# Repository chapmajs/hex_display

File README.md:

PIC Based Mutiplexed 7-segment LED Display
==========================================

A project to drive multiplexed 7-segment LED displays as hex displays using a Microchip PIC18F6310 with a minimum of external components. This is a work in progress!

This project is released as [Open Source Hardware (OSHW)](http://freedomdefined.org/OSHW). All hardware contained within this repository are covered by a [Creative Commons Attribution-ShareAlike 3.0 license (CC BY-SA 3.0)](http://creativecommons.org/licenses/by-sa/3.0/). Firmware and software are licensed under GPLv3 -- see LICENSE and GPL-3.0 for more information.

### Current Status

Rev 0 PC board has been tested, sample firmware in this repository displays 'deadbeef'. Minor tweaks to the PC board layout are required for 0.1" perfboard compatibility. 24-bit port input has not yet been tested.

### Why?

"Intelligent" single-nybble hexadecimal displays like the TIL311 are available, as well as 7-segment hex decoders; however, these devices are no longer in production and they're expensive, when you can find them. The 7-segment hex decoders that are currently available handle single displays only and don't work with multi-character multiplexed displays.

### How?

This display project implements a multi-character bitmapped display using an interrupt-driven subroutine to handle multiplexing. A display buffer is used to simplify loading data for display. Character selection was delegated to a subroutine that enables the appropriate cathode driver pin based on an offset. This allows the size of the display to be changed with minimal firmware modification.

A PIC microcontroller with plenty of I/O was chosen to allow input of 24 bits of binary data in parallel (16 bit address + 8 bit data, a common arrangement with old 8-bit processors like the Intel 8080/8085, Zilog Z80, or MOS 6502). Using this device as a debugging tool was the primary goal; however, it was designed in such a way that the PIC's onboard devices can also act as data sources for the display. It's possible to display data from I2C, SPI, RS-232, parallel port, or ADC sources. Additionally, one could drive dot matrix displays with the same firmware.

An in-memory lookup table provides translation from single hex nybbles to appropriate bitmap patterns for 7-segment displays. A routine utilizing this table can be called from firmware to produce hex digits if bitmap characters are not desired.

### Who?

[The Glitch Works](http://www.glitchwrks.com/)

There's a thread on the [BinRev Forums](http://www.binrev.com/forums/index.php/topic/46160-hex-display-project/) for discussion

### Files

* display.asm: PIC18F6310 firmware for driving mutiplexed common cathode 7-segment displays
* pinouts.md: PC board connector pinouts
* schematic.sch: Eagle CAD schematic
* schematic.brd: Eagle CAD board layout
* eagle_libs: Directory containing nonstandard Eagle CAD parts

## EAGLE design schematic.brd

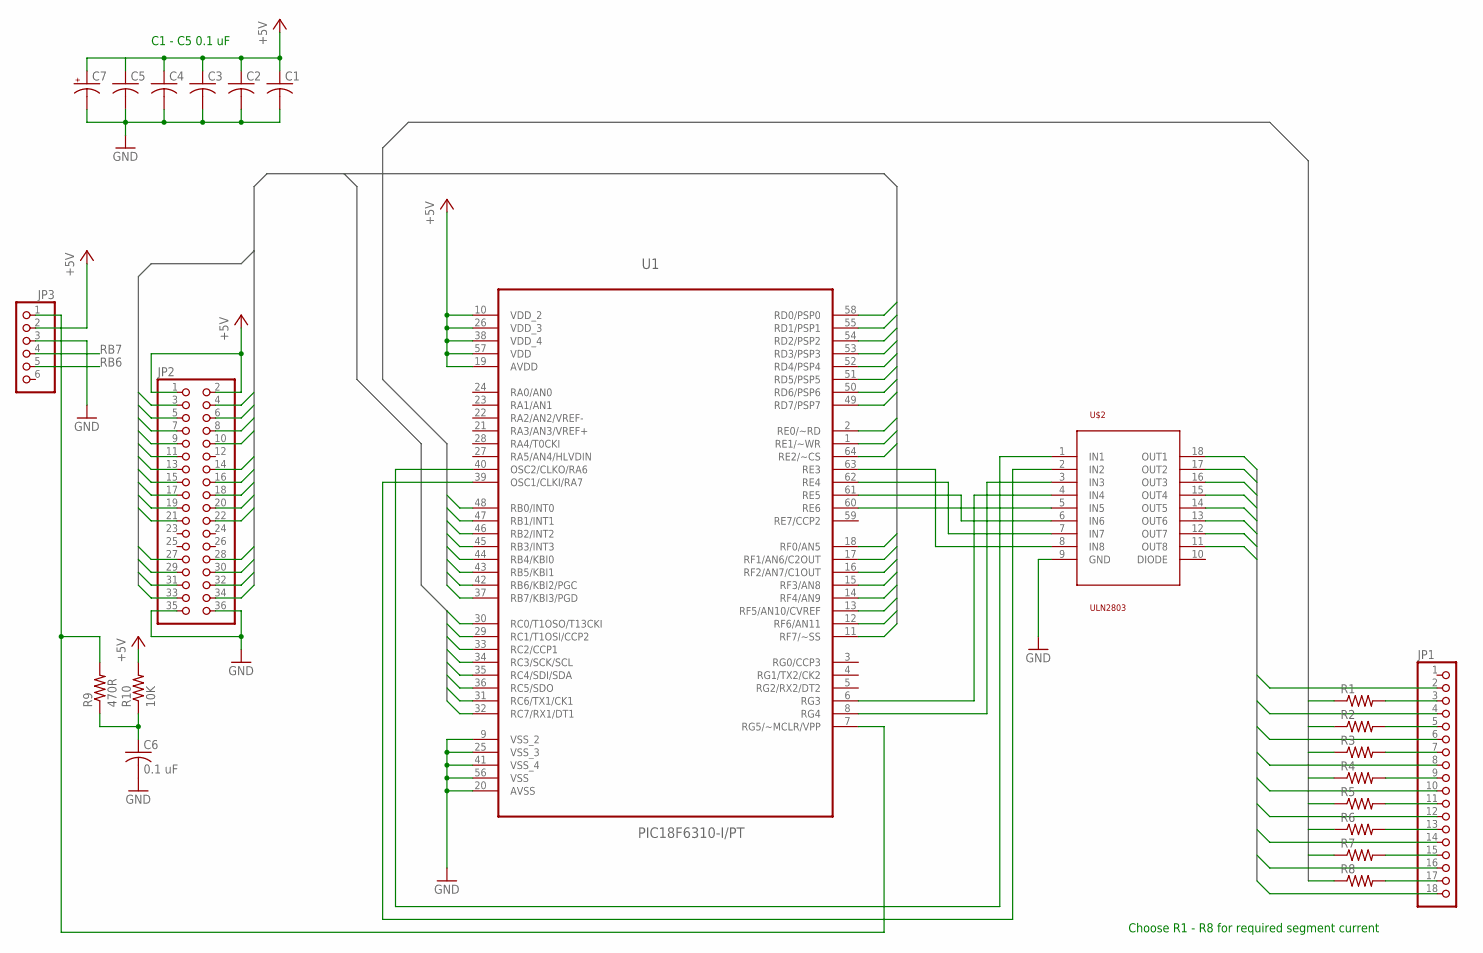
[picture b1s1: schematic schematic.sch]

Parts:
C1, C2, C3, C4, C5: C-USC0603K; C0603K
C6: 0.1 uF; C0603K
C7: CPOL-USB/3528-21W; B/3528-21W
JP1: PINHD-1X18; 1X18
JP2: PINHD-2X18; 2X18
JP3: PINHD-1X6; 1X06
R1, R2, R3, R4, R5, R6, R7, R8: R-US_R0603; R0603
R9: 470R; R0603
R10: 10K; R0603
U1: PIC18F6310-I/PT; QFP50P1200X1200X120-64N
U$2: ULN2803; SO18L

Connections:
+5V: C1.1, C2.1, C3.1, C4.1, C5.1, C7.+, JP2.1, JP2.2, JP3.2, R10.2, U1.10 (VDD_2), U1.19 (AVDD), U1.26 (VDD_3), U1.38 (VDD_4), U1.57 (VDD)
DIGIT0: JP1.2
DIGIT1: JP1.4, U$2.18 (OUT1)
DIGIT2: JP1.6, U$2.17 (OUT2)
DIGIT3: JP1.8, U$2.16 (OUT3)
DIGIT4: JP1.10, U$2.15 (OUT4)
DIGIT5: JP1.12, U$2.14 (OUT5)
DIGIT6: JP1.14, U$2.13 (OUT6)
DIGIT7: JP1.16, U$2.12 (OUT7)
DIGIT8: JP1.18, U$2.11 (OUT8)
GND: C1.2, C2.2, C3.2, C4.2, C5.2, C6.2, C7.-, JP2.35, JP2.36, JP3.3, U1.9 (VSS_2), U1.20 (AVSS), U1.25 (VSS_3), U1.41 (VSS_4), U1.56 (VSS), U$2.9 (GND)
unnamed: U1.63 (RE3), U$2.8 (IN8)
unnamed: U1.62 (RE4), U$2.7 (IN7)
unnamed: U1.61 (RE5), U$2.6 (IN6)
unnamed: U1.60 (RE6), U$2.5 (IN5)
unnamed: U1.40 (OSC2/CLKO/RA6), U$2.1 (IN1)
unnamed: U1.39 (OSC1/CLKI/RA7), U$2.2 (IN2)
unnamed: U1.6 (RG3), U$2.4 (IN4)
unnamed: U1.8 (RG4), U$2.3 (IN3)
unnamed: JP3.1, R9.2, U1.7 (RG5/~MCLR/VPP)
unnamed: JP1.3, R1.2
unnamed: JP1.5, R2.2
unnamed: JP1.7, R3.2
unnamed: JP1.9, R4.2
unnamed: JP1.11, R5.2
unnamed: C6.1, R9.1, R10.1
unnamed: JP1.13, R6.2
unnamed: JP1.15, R7.2
unnamed: JP1.17, R8.2
RB0: R1.1, U1.48 (RB0/INT0)
RB1: R2.1, U1.47 (RB1/INT1)
RB2: R3.1, U1.46 (RB2/INT2)
RB3: R4.1, U1.45 (RB3/INT3)
RB4: R5.1, U1.44 (RB4/KBI0)
RB5: R6.1, U1.43 (RB5/KBI1)
RB6: JP3.5, R7.1, U1.42 (RB6/KBI2/PGC)
RB7: JP3.4, R8.1, U1.37 (RB7/KBI3/PGD)
RC0: JP2.27, U1.30 (RC0/T1OSO/T13CKI)
RC1: JP2.28, U1.29 (RC1/T1OSI/CCP2)
RC2: JP2.29, U1.33 (RC2/CCP1)
RC3: JP2.30, U1.34 (RC3/SCK/SCL)
RC4: JP2.31, U1.35 (RC4/SDI/SDA)
RC5: JP2.32, U1.36 (RC5/SDO)
RC6: JP2.33, U1.31 (RC6/TX1/CK1)
RC7: JP2.34, U1.32 (RC7/RX1/DT1)
RD0: JP2.3, U1.58 (RD0/PSP0)
RD1: JP2.4, U1.55 (RD1/PSP1)
RD2: JP2.5, U1.54 (RD2/PSP2)
RD3: JP2.6, U1.53 (RD3/PSP3)
RD4: JP2.7, U1.52 (RD4/PSP4)
RD5: JP2.8, U1.51 (RD5/PSP5)
RD6: JP2.9, U1.50 (RD6/PSP6)
RD7: JP2.10, U1.49 (RD7/PSP7)
RE0: JP2.13, U1.2 (RE0/~RD)
RE1: JP2.14, U1.1 (RE1/~WR)
RE2: JP2.11, U1.64 (RE2/~CS)
RF0: JP2.15, U1.18 (RF0/AN5)
RF1: JP2.16, U1.17 (RF1/AN6/C2OUT)
RF2: JP2.17, U1.16 (RF2/AN7/C1OUT)
RF3: JP2.18, U1.15 (RF3/AN8)
RF4: JP2.19, U1.14 (RF4/AN9)
RF5: JP2.20, U1.13 (RF5/AN10/CVREF)
RF6: JP2.21, U1.12 (RF6/AN11)
RF7: JP2.22, U1.11 (RF7/~SS)

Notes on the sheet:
C1 - C5 0.1 uF
Choose R1 - R8 for required segment current

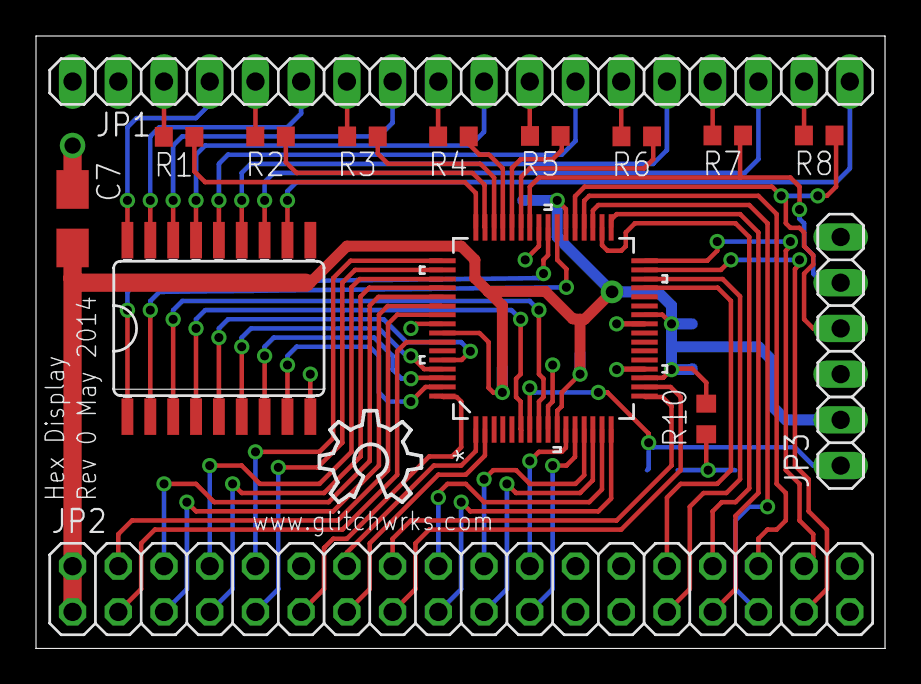
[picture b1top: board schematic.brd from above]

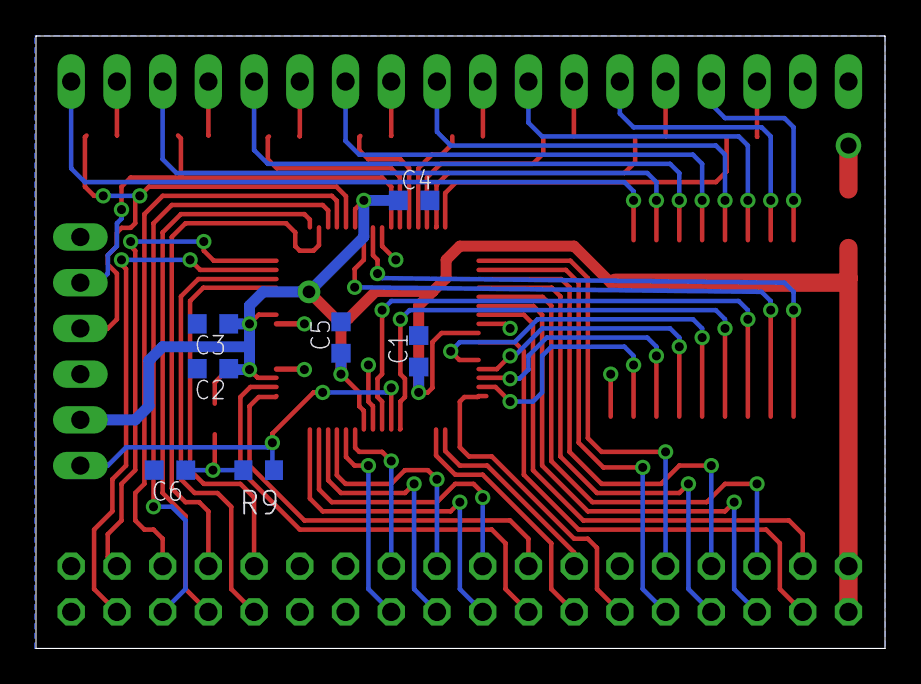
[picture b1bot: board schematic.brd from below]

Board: 2 copper layers, 47.2 x 34.0 mm, 23 parts (7 on the bottom side), 63 nets.

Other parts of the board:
U$1: OSHW_8X200_NOTEXT

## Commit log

2013-08-27 WIP initial commit
2013-08-27 Moving license files around
2013-08-27 Cleaning up source
2013-08-27 increasing display to 8 digits and adding input from Port C
2013-08-28 Adding project description
2013-08-28 Reducing level of subheaders
2013-09-03 Adding image of display output
2014-05-01 Adding rev 0 schematic and board
2014-05-01 Adding board/schematic to README
2014-05-14 Adding comments, cleanup, updating for rev 0 PC board
2014-05-14 Adding pinouts for rev 0 board
2014-05-14 Updating year in LICENSE
2014-05-14 Adding status, segment table explanation, link to binrev to README
2014-05-14 Adding reference to pinouts to README
2014-05-14 Updating schematic, board
2014-05-14 Adding EAGLE libs for PIC18F6310 and ULN2803
2014-05-14 Adding license notes to README.md
2014-05-14 Fixing OSHW link
2014-05-14 Adding note about Eagle parts to README
2014-05-14 Adding rev0 board image
